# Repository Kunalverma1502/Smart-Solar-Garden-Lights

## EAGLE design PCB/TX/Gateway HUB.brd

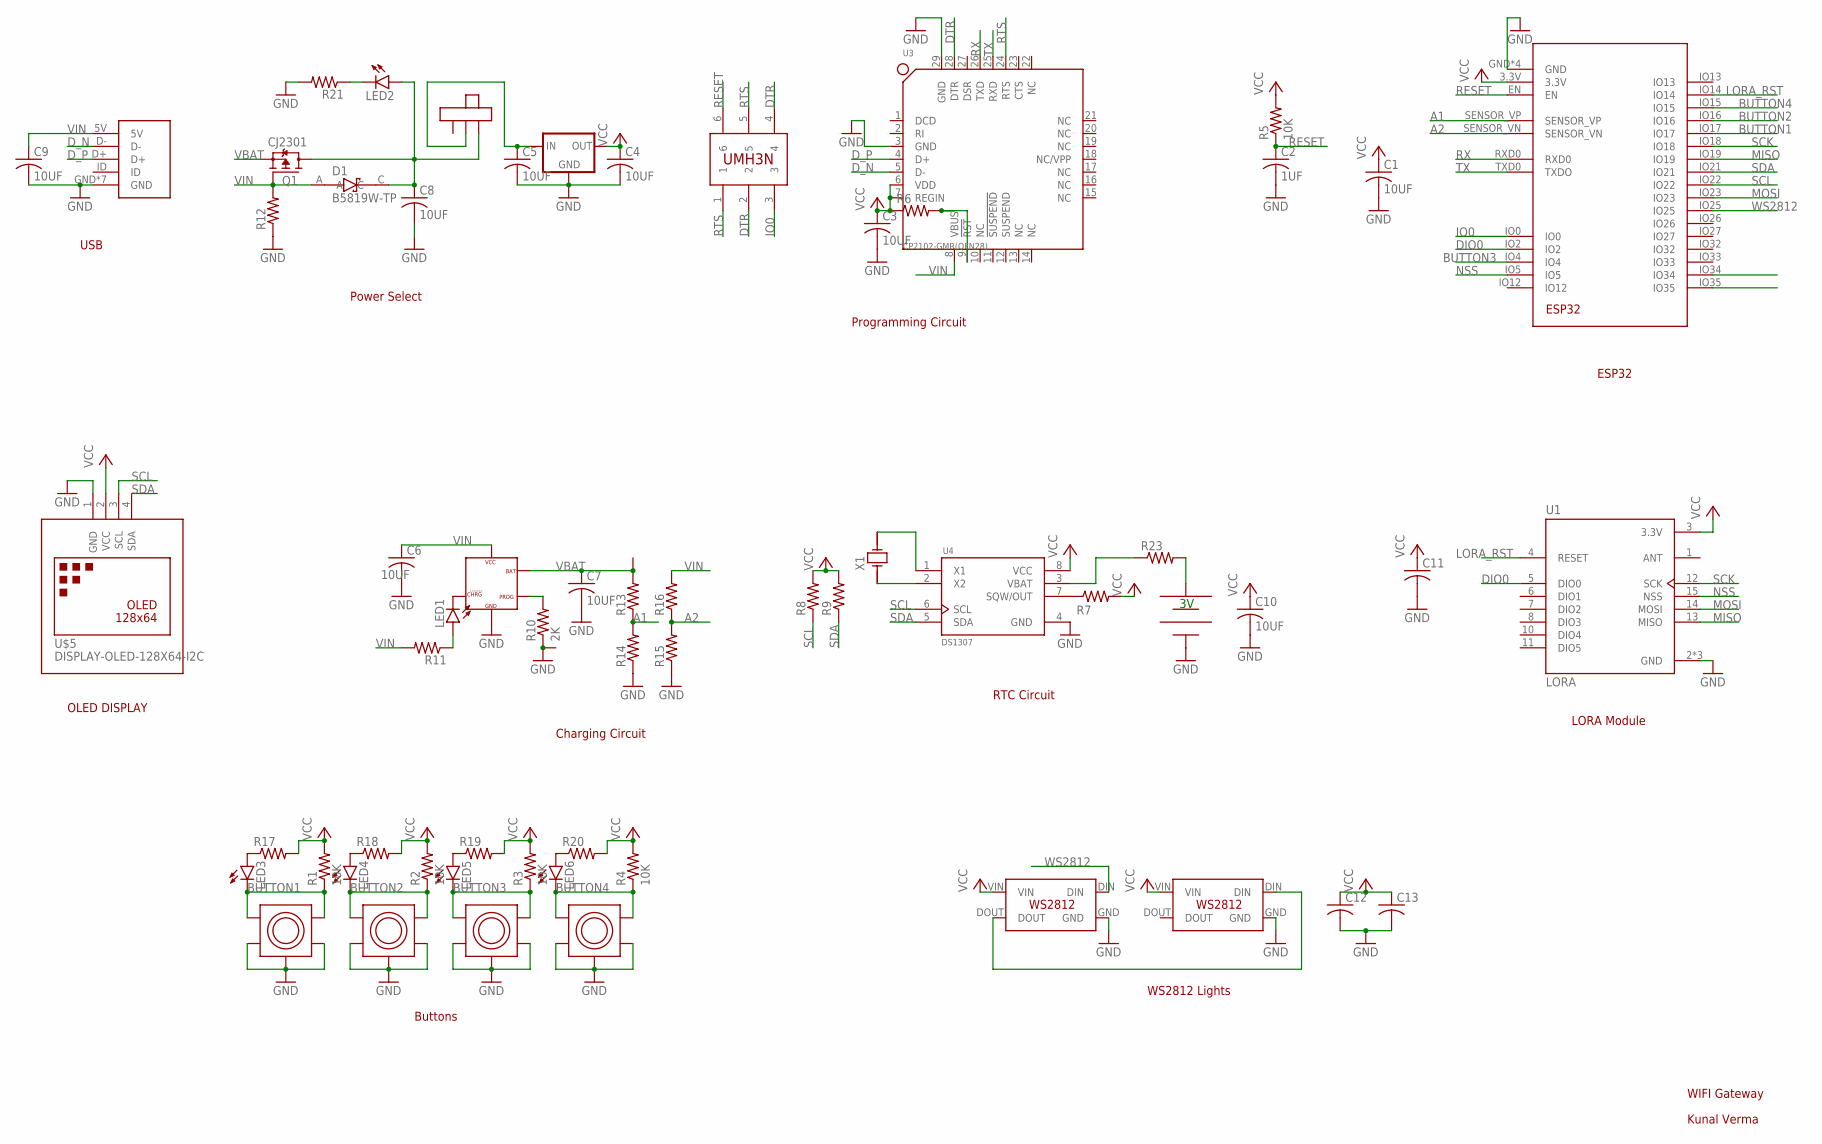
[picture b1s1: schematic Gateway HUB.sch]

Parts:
C1, C3, C4, C5, C6, C7, C8, C9, C10: 10UF; C0603
C2: 1UF; C0603
C11, C12, C13: C-USC0603; C0603
D1: B5819W-TP; SOD3716X135N
IC1: V_REG3.3MP; SOT223
LED1, LED2, LED3, LED4, LED5, LED6: LEDSML0603; SML0603
Q1: CJ2301; SOT95P230X110-3N
R1, R2, R3, R4, R5: 10K; R0603
R6, R7, R8, R9, R11, R12, R13, R14, R15, R16, R17, R18, R19, R20, R21, R23: R-US_R0603; R0603
R10: 2K; R0603
U1: LORA; XCVR_RA-01H
U2: ESP32; MODULE_ESP-WROOM-32
U3: CP2102-GMR(QFN28); QFN28G_0.5-5X5MM
U4: DS1307; SOIC127P600X175-8N
U5: TP4054; SOT23-3
U$1, U$2, U$3, U$4: PUSHBUTTON; B3W-4105
U$5: DISPLAY-OLED-128X64-I2C
U$6: COIN_CELL_HOLDER; CR2032-BS-6-1
U$7: UMH3N
U$8: MICROUSB; USB
U$9: SELF-TOOGLE-SWITCH
U$10, U$11: PAD; PADS
U$12, U$13: WS2812SMD-2020; SMD-2020
X1: CRYSTAL_38T-32.768KHZ; XTAL_AB38T-32.768KHZ

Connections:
A1: R13.1, R14.2, U2.SENSOR_VP
A2: R15.2, R16.1, U2.SENSOR_VN
BUTTON1: LED3.C, R1.1, U2.IO17, U$1.P$1, U$1.P$4
BUTTON2: LED4.C, R2.1, U2.IO16, U$2.P$1, U$2.P$4
BUTTON3: LED5.C, R3.1, U2.IO4, U$3.P$1, U$3.P$4
BUTTON4: LED6.C, R4.1, U2.IO15, U$4.P$1, U$4.P$4
DIO0: U1.5 (DIO0), U2.IO2
DTR: U3.28 (DTR), U$7.2, U$7.4
D_N: U3.5 (D-), U$8.D-
D_P: U3.4 (D+), U$8.D+
GND: C1.2, C2.2, C3.2, C4.2, C5.2, C6.2, C7.2, C8.2, C9.2, C10.2, C11.2, C12.2, C13.2, IC1.GND, R10.1, R12.1, R14.1, R15.1, R21.2, U1.2 (GND), U1.9 (GND), U1.16 (GND), U2.GND, U2.GND1 (GND), U2.GND2 (GND), U2.GND3 (GND), U3.3 (GND), U3.29 (GND), U4.4 (GND), U5.2, U$1.P$2, U$1.P$3, U$1.P$5, U$2.P$2, U$2.P$3, U$2.P$5, U$3.P$2, U$3.P$3, U$3.P$5, U$4.P$2, U$4.P$3, U$4.P$5, U$5.1 (GND), U$6.-, U$8.GND, U$8.GND1 (GND), U$8.GND2 (GND), U$8.GND3 (GND), U$8.GND4 (GND), U$8.GND5 (GND), U$8.GND6 (GND), U$11.P$1, U$12.GND, U$13.GND
IO0: U2.IO0, U$7.3
LORA_RST: U1.4 (RESET), U2.IO14
MISO: U1.13 (MISO), U2.IO19
MOSI: U1.14 (MOSI), U2.IO23
unnamed: R23.1, U4.3 (VBAT)
unnamed: R6.2, U3.9 (!RST)
unnamed: R7.1, U4.7 (SQW/OUT)
unnamed: C5.1, IC1.VIN (IN), U$9.2
unnamed: U4.2 (X2), X1.1
unnamed: U4.1 (X1), X1.2
unnamed: R10.2, U5.5
unnamed: LED1.C, U5.1
unnamed: C8.1, D1.C, LED2.A, Q1.3 (D), U$9.3
unnamed: LED1.A, R11.1
unnamed: LED3.A, R17.1
unnamed: LED4.A, R18.1
unnamed: LED5.A, R19.1
unnamed: LED6.A, R20.1
unnamed: LED2.C, R21.1
unnamed: U$12.DOUT, U$13.DIN
unnamed: R23.2, U$6.+
NSS: U1.15 (NSS), U2.IO5
RESET: C2.1, R5.1, U2.EN, U$7.6
RTS: U3.24 (RTS), U$7.1, U$7.5
RX: U2.RXD0, U3.26 (TXD)
SCK: U1.12 (SCK), U2.IO18
SCL: R8.1, U2.IO22, U4.6 (SCL), U$5.3 (SCL)
SDA: R9.1, U2.IO21, U4.5 (SDA), U$5.4 (SDA)
TX: U2.TXD0 (TXDO), U3.25 (RXD)
VBAT: C7.1, Q1.2 (S), R13.2, U5.3, U$10.P$1
VCC: C1.1, C3.1, C4.1, C10.1, C11.1, C12.1, C13.1, IC1.VOUT (OUT), IC1.VOUT1 (OUT), R1.2, R2.2, R3.2, R4.2, R5.2, R6.1, R7.2, R8.2, R9.2, R17.2, R18.2, R19.2, R20.2, U1.3 (3.3V), U2.3.3V, U3.6 (VDD), U3.7 (REGIN), U4.8 (VCC), U$5.2 (VCC), U$12.VIN, U$13.VIN
VIN: C6.1, C9.1, D1.A, Q1.1 (G), R11.2, R12.2, R16.2, U3.8 (VBUS), U5.4, U$8.5V
WS2812: U2.IO25, U$12.DIN

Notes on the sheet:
WIFI Gateway
Kunal Verma
Buttons
WS2812 Lights
OLED DISPLAY
Charging Circuit
RTC Circuit
LORA Module
ESP32
Programming Circuit
Power Select
USB

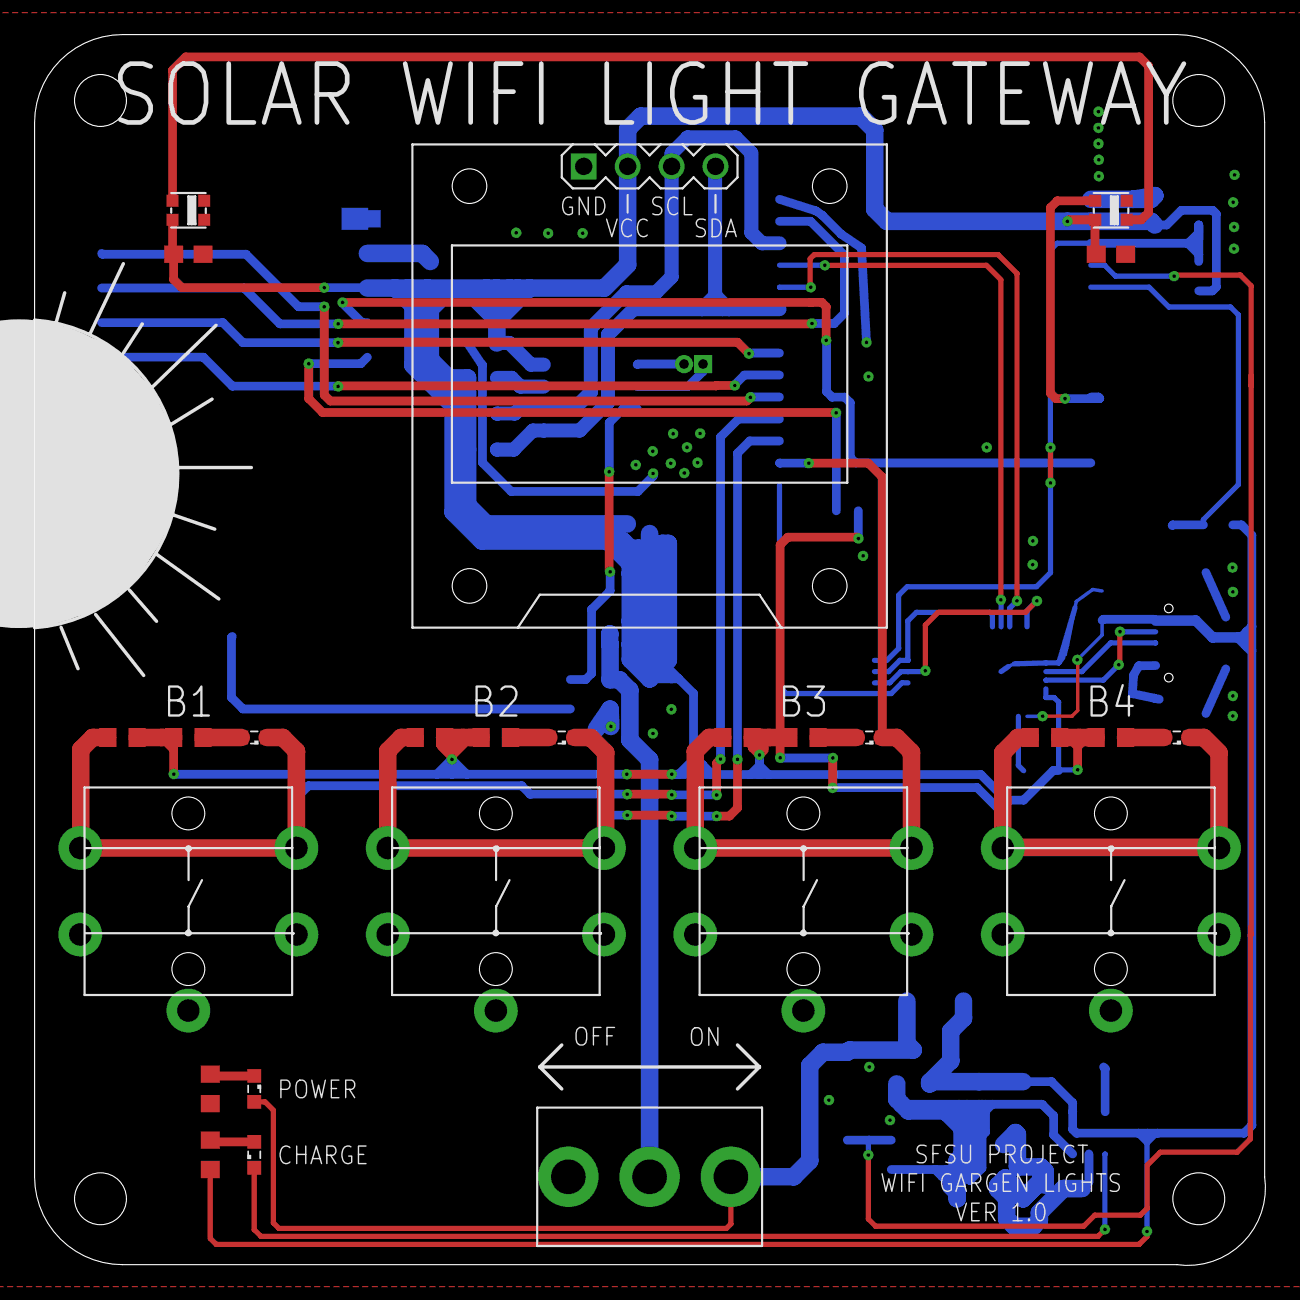
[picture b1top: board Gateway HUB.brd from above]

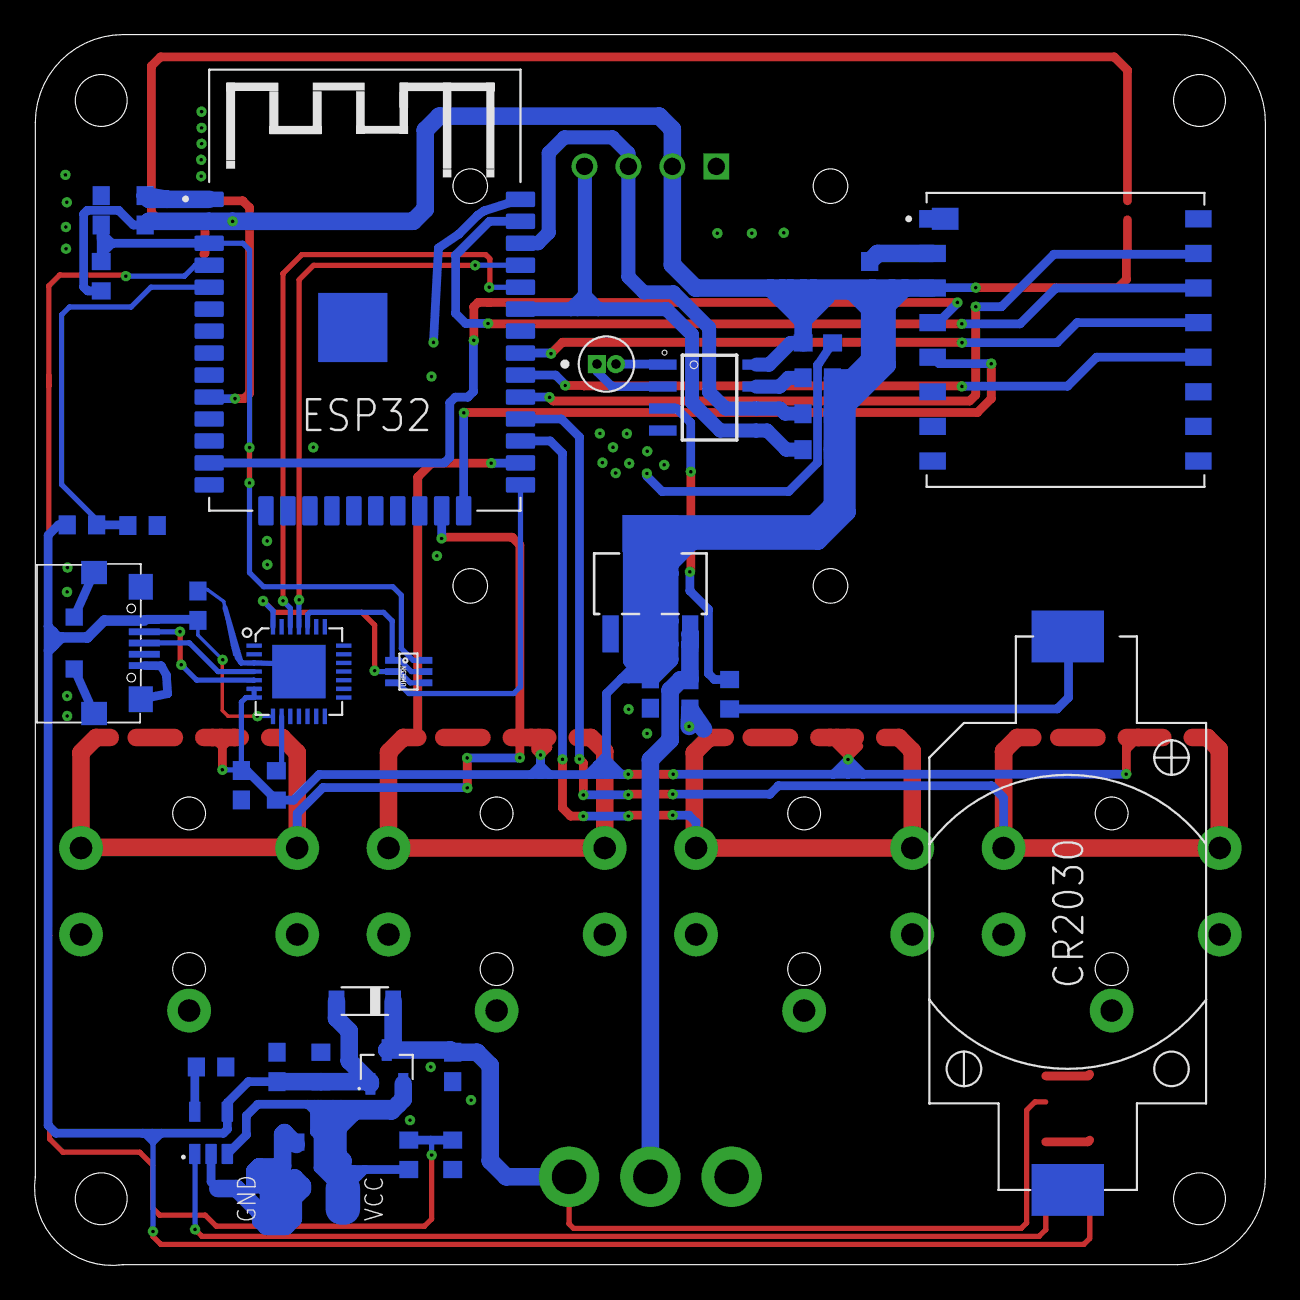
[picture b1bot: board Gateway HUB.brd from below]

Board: 2 copper layers, 71.2 x 71.2 mm, 63 parts (37 on the bottom side), 44 nets.

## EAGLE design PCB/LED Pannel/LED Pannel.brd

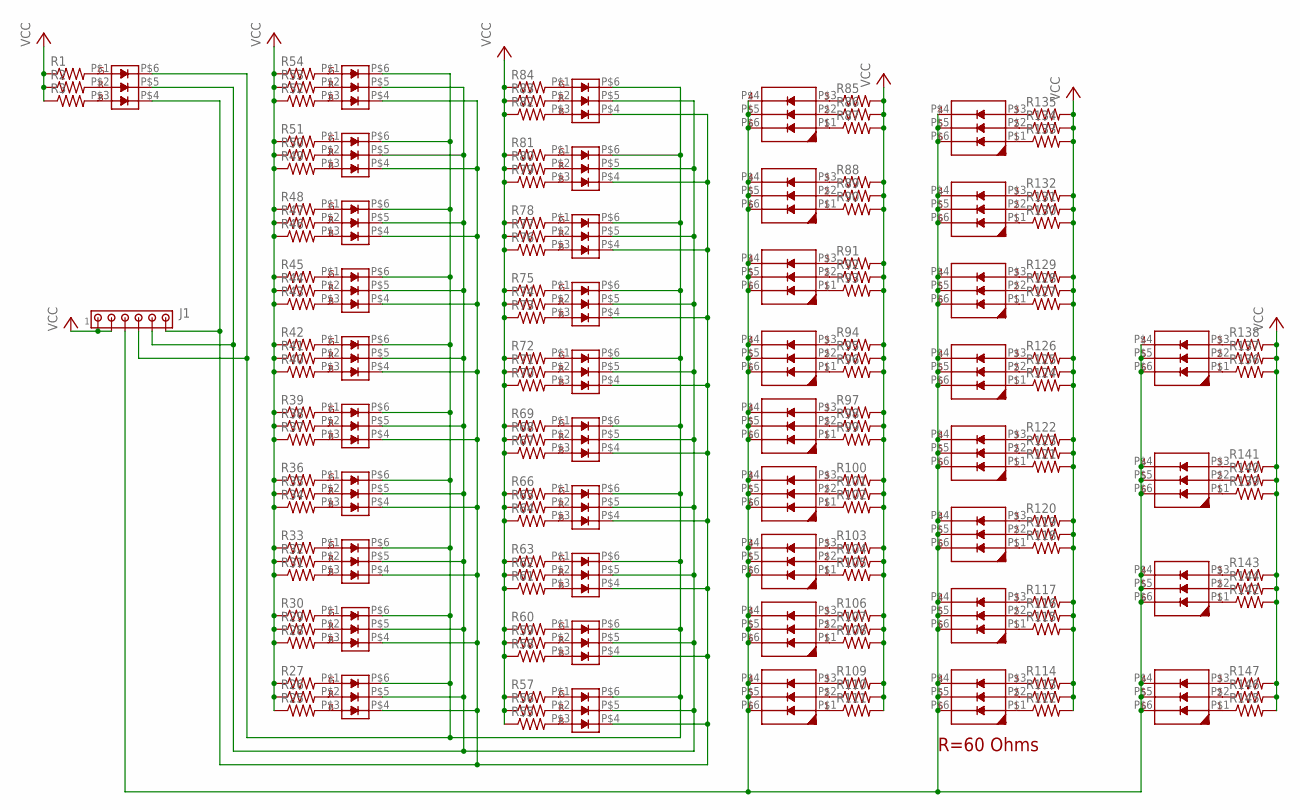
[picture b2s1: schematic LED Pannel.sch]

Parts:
J1: MTA06-156; 1X6MTA
R1, R2, R3, R25, R26, R27, R28, R29, R30, R31, R32, R33, R34, R35, R36, R37, R38, R39, R40, R41, R42, R43, R44, R45, R46, R47, R48, R49, R50, R51, R52, R53, R54, R55, R56, R57, R58, R59, R60, R61, R62, R63, R64, R65, R66, R67, R68, R69, R70, R71, R72, R73, R74, R75, R76, R77, R78, R79, R80, R81, R82, R83, R84, R85, R86, R87, R88, R89, R90, R91, R92, R93, R94, R95, R96, R97, R98, R99, R100, R101, R102, R103, R104, R105, R106, R107, R108, R109, R110, R111, R112, R113, R114, R115, R116, R117, R118, R119, R120, R121, R122, R123, R124, R125, R126, R127, R128, R129, R130, R131, R132, R133, R134, R135, R136, R137, R138, R139, R140, R141, R142, R143, R144, R145, R146, R147: R-US_R0603; R0603
U$1, U$2, U$3, U$4, U$5, U$6, U$7, U$8, U$9, U$10, U$17, U$18, U$19, U$20, U$21, U$22, U$23, U$24, U$25, U$26, U$27: RGB_LED; 5050
U$11, U$12, U$13, U$14, U$15, U$16, U$35, U$36, U$37, U$38, U$47, U$48, U$49, U$50, U$51, U$52, U$53, U$54, U$55, U$56, U$57: WHITE_LED; 5050

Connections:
unnamed: R1.2, U$27.P$1
unnamed: R2.2, U$27.P$2
unnamed: R3.2, U$27.P$3
unnamed: J1.4, U$1.P$6, U$2.P$6, U$3.P$6, U$4.P$6, U$5.P$6, U$6.P$6, U$7.P$6, U$8.P$6, U$9.P$6, U$10.P$6, U$17.P$6, U$18.P$6, U$19.P$6, U$20.P$6, U$21.P$6, U$22.P$6, U$23.P$6, U$24.P$6, U$25.P$6, U$26.P$6, U$27.P$6
unnamed: J1.5, U$1.P$5, U$2.P$5, U$3.P$5, U$4.P$5, U$5.P$5, U$6.P$5, U$7.P$5, U$8.P$5, U$9.P$5, U$10.P$5, U$17.P$5, U$18.P$5, U$19.P$5, U$20.P$5, U$21.P$5, U$22.P$5, U$23.P$5, U$24.P$5, U$25.P$5, U$26.P$5, U$27.P$5
unnamed: J1.6, U$1.P$4, U$2.P$4, U$3.P$4, U$4.P$4, U$5.P$4, U$6.P$4, U$7.P$4, U$8.P$4, U$9.P$4, U$10.P$4, U$17.P$4, U$18.P$4, U$19.P$4, U$20.P$4, U$21.P$4, U$22.P$4, U$23.P$4, U$24.P$4, U$25.P$4, U$26.P$4, U$27.P$4
unnamed: J1.3, U$11.P$4, U$11.P$5, U$11.P$6, U$12.P$4, U$12.P$5, U$12.P$6, U$13.P$4, U$13.P$5, U$13.P$6, U$14.P$4, U$14.P$5, U$14.P$6, U$15.P$4, U$15.P$5, U$15.P$6, U$16.P$4, U$16.P$5, U$16.P$6, U$35.P$4, U$35.P$5, U$35.P$6, U$36.P$4, U$36.P$5, U$36.P$6, U$37.P$4, U$37.P$5, U$37.P$6, U$38.P$4, U$38.P$5, U$38.P$6, U$47.P$4, U$47.P$5, U$47.P$6, U$48.P$4, U$48.P$5, U$48.P$6, U$49.P$4, U$49.P$5, U$49.P$6, U$50.P$4, U$50.P$5, U$50.P$6, U$51.P$4, U$51.P$5, U$51.P$6, U$52.P$4, U$52.P$5, U$52.P$6, U$53.P$4, U$53.P$5, U$53.P$6, U$54.P$4, U$54.P$5, U$54.P$6, U$55.P$4, U$55.P$5, U$55.P$6, U$56.P$4, U$56.P$5, U$56.P$6, U$57.P$4, U$57.P$5, U$57.P$6
unnamed: R25.2, U$26.P$3
unnamed: R26.2, U$26.P$2
unnamed: R28.2, U$25.P$3
unnamed: R29.2, U$25.P$2
unnamed: R30.2, U$25.P$1
unnamed: R27.2, U$26.P$1
unnamed: R31.2, U$24.P$3
unnamed: R32.2, U$24.P$2
unnamed: R33.2, U$24.P$1
unnamed: R34.2, U$23.P$3
unnamed: R35.2, U$23.P$2
unnamed: R36.2, U$23.P$1
unnamed: R37.2, U$22.P$3
unnamed: R38.2, U$22.P$2
unnamed: R39.2, U$22.P$1
unnamed: R40.2, U$21.P$3
unnamed: R41.2, U$21.P$2
unnamed: R42.2, U$21.P$1
unnamed: R43.2, U$20.P$3
unnamed: R44.2, U$20.P$2
unnamed: R45.2, U$20.P$1
unnamed: R46.2, U$19.P$3
unnamed: R47.2, U$19.P$2
unnamed: R48.2, U$19.P$1
unnamed: R49.2, U$18.P$3
unnamed: R50.2, U$18.P$2
unnamed: R51.2, U$18.P$1
unnamed: R52.2, U$17.P$3
unnamed: R53.2, U$17.P$2
unnamed: R54.2, U$17.P$1
unnamed: R56.2, U$1.P$2
unnamed: R57.2, U$1.P$1
unnamed: R55.2, U$1.P$3
unnamed: R58.2, U$2.P$3
unnamed: R59.2, U$2.P$2
unnamed: R60.2, U$2.P$1
unnamed: R61.2, U$3.P$3
unnamed: R62.2, U$3.P$2
unnamed: R63.2, U$3.P$1
unnamed: R64.2, U$4.P$3
unnamed: R65.2, U$4.P$2
unnamed: R66.2, U$4.P$1
unnamed: R68.2, U$5.P$2
unnamed: R69.2, U$5.P$1
unnamed: R67.2, U$5.P$3
unnamed: R70.2, U$6.P$3
unnamed: R71.2, U$6.P$2
unnamed: R72.2, U$6.P$1
unnamed: R73.2, U$7.P$3
unnamed: R74.2, U$7.P$2
unnamed: R75.2, U$7.P$1
unnamed: R76.2, U$8.P$3
unnamed: R77.2, U$8.P$2
unnamed: R78.2, U$8.P$1
unnamed: R79.2, U$9.P$3
unnamed: R80.2, U$9.P$2
unnamed: R81.2, U$9.P$1
unnamed: R82.2, U$10.P$3
unnamed: R83.2, U$10.P$2
unnamed: R84.2, U$10.P$1
unnamed: R85.1, U$49.P$3
unnamed: R86.1, U$49.P$2
unnamed: R87.1, U$49.P$1
unnamed: R88.1, U$48.P$3
unnamed: R89.1, U$48.P$2
unnamed: R90.1, U$48.P$1
unnamed: R91.1, U$47.P$3
unnamed: R92.1, U$47.P$2
unnamed: R93.1, U$47.P$1
unnamed: R95.1, U$16.P$2
unnamed: R96.1, U$16.P$1
unnamed: R94.1, U$16.P$3
unnamed: R97.1, U$15.P$3
unnamed: R98.1, U$15.P$2
unnamed: R99.1, U$15.P$1
unnamed: R100.1, U$14.P$3
unnamed: R101.1, U$14.P$2
unnamed: R102.1, U$14.P$1
unnamed: R103.1, U$13.P$3
unnamed: R104.1, U$13.P$2
unnamed: R105.1, U$13.P$1
unnamed: R106.1, U$12.P$3
unnamed: R107.1, U$12.P$2
unnamed: R108.1, U$12.P$1
unnamed: R109.1, U$11.P$3
unnamed: R110.1, U$11.P$2
unnamed: R111.1, U$11.P$1
unnamed: R112.1, U$57.P$1
unnamed: R113.1, U$57.P$2
unnamed: R114.1, U$57.P$3
unnamed: R115.1, U$56.P$1
unnamed: R116.1, U$56.P$2
unnamed: R117.1, U$56.P$3
unnamed: R118.1, U$55.P$1
unnamed: R119.1, U$55.P$2
unnamed: R120.1, U$55.P$3
unnamed: R121.1, U$54.P$1
unnamed: R122.1, U$54.P$3
unnamed: R123.1, U$54.P$2
unnamed: R124.1, U$53.P$1
unnamed: R125.1, U$53.P$2
unnamed: R126.1, U$53.P$3
unnamed: R127.1, U$52.P$1
unnamed: R128.1, U$52.P$2
unnamed: R129.1, U$52.P$3
unnamed: R130.1, U$51.P$1
unnamed: R131.1, U$51.P$2
unnamed: R132.1, U$51.P$3
unnamed: R133.1, U$50.P$1
unnamed: R134.1, U$50.P$2
unnamed: R135.1, U$50.P$3
unnamed: R136.1, U$38.P$1
unnamed: R137.1, U$38.P$2
unnamed: R138.1, U$38.P$3
unnamed: R139.1, U$37.P$1
unnamed: R140.1, U$37.P$2
unnamed: R141.1, U$37.P$3
unnamed: R142.1, U$36.P$1
unnamed: R143.1, U$36.P$3
unnamed: R144.1, U$36.P$2
unnamed: R145.1, U$35.P$1
unnamed: R146.1, U$35.P$2
unnamed: R147.1, U$35.P$3
VCC: J1.1, J1.2, R1.1, R2.1, R3.1, R25.1, R26.1, R27.1, R28.1, R29.1, R30.1, R31.1, R32.1, R33.1, R34.1, R35.1, R36.1, R37.1, R38.1, R39.1, R40.1, R41.1, R42.1, R43.1, R44.1, R45.1, R46.1, R47.1, R48.1, R49.1, R50.1, R51.1, R52.1, R53.1, R54.1, R55.1, R56.1, R57.1, R58.1, R59.1, R60.1, R61.1, R62.1, R63.1, R64.1, R65.1, R66.1, R67.1, R68.1, R69.1, R70.1, R71.1, R72.1, R73.1, R74.1, R75.1, R76.1, R77.1, R78.1, R79.1, R80.1, R81.1, R82.1, R83.1, R84.1, R85.2, R86.2, R87.2, R88.2, R89.2, R90.2, R91.2, R92.2, R93.2, R94.2, R95.2, R96.2, R97.2, R98.2, R99.2, R100.2, R101.2, R102.2, R103.2, R104.2, R105.2, R106.2, R107.2, R108.2, R109.2, R110.2, R111.2, R112.2, R113.2, R114.2, R115.2, R116.2, R117.2, R118.2, R119.2, R120.2, R121.2, R122.2, R123.2, R124.2, R125.2, R126.2, R127.2, R128.2, R129.2, R130.2, R131.2, R132.2, R133.2, R134.2, R135.2, R136.2, R137.2, R138.2, R139.2, R140.2, R141.2, R142.2, R143.2, R144.2, R145.2, R146.2, R147.2

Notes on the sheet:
R=60 Ohms

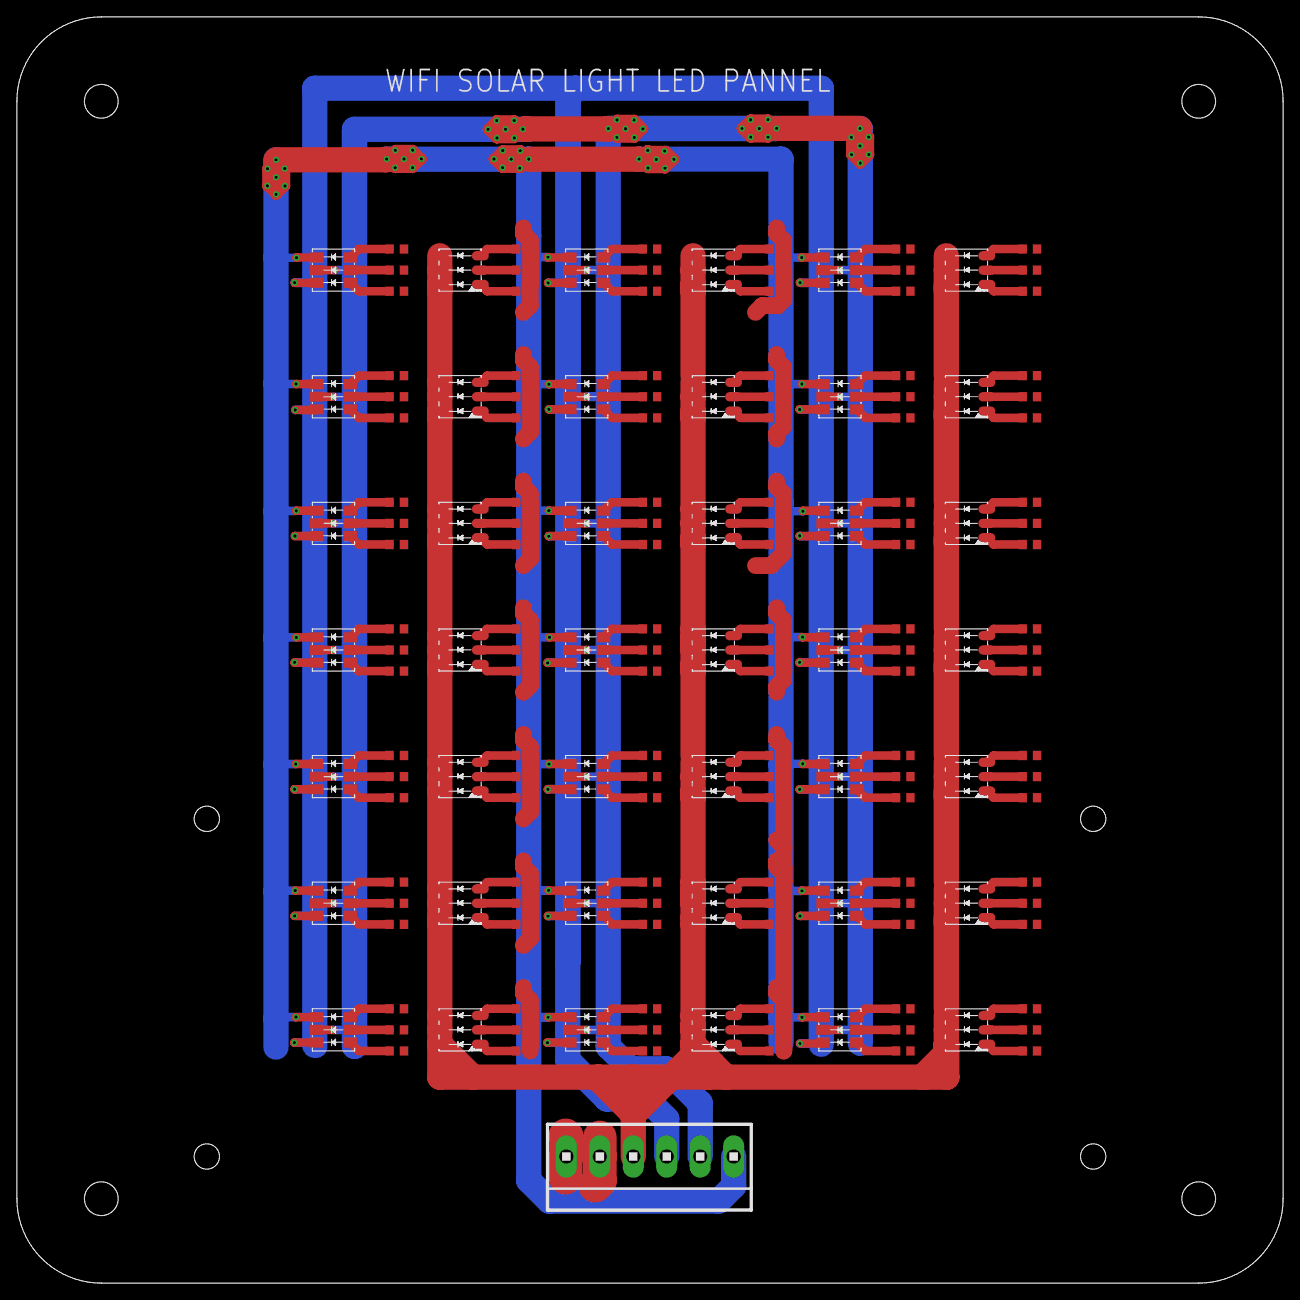
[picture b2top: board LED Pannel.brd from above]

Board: 2 copper layers, 150.0 x 150.0 mm, 169 parts (0 on the bottom side), 131 nets.

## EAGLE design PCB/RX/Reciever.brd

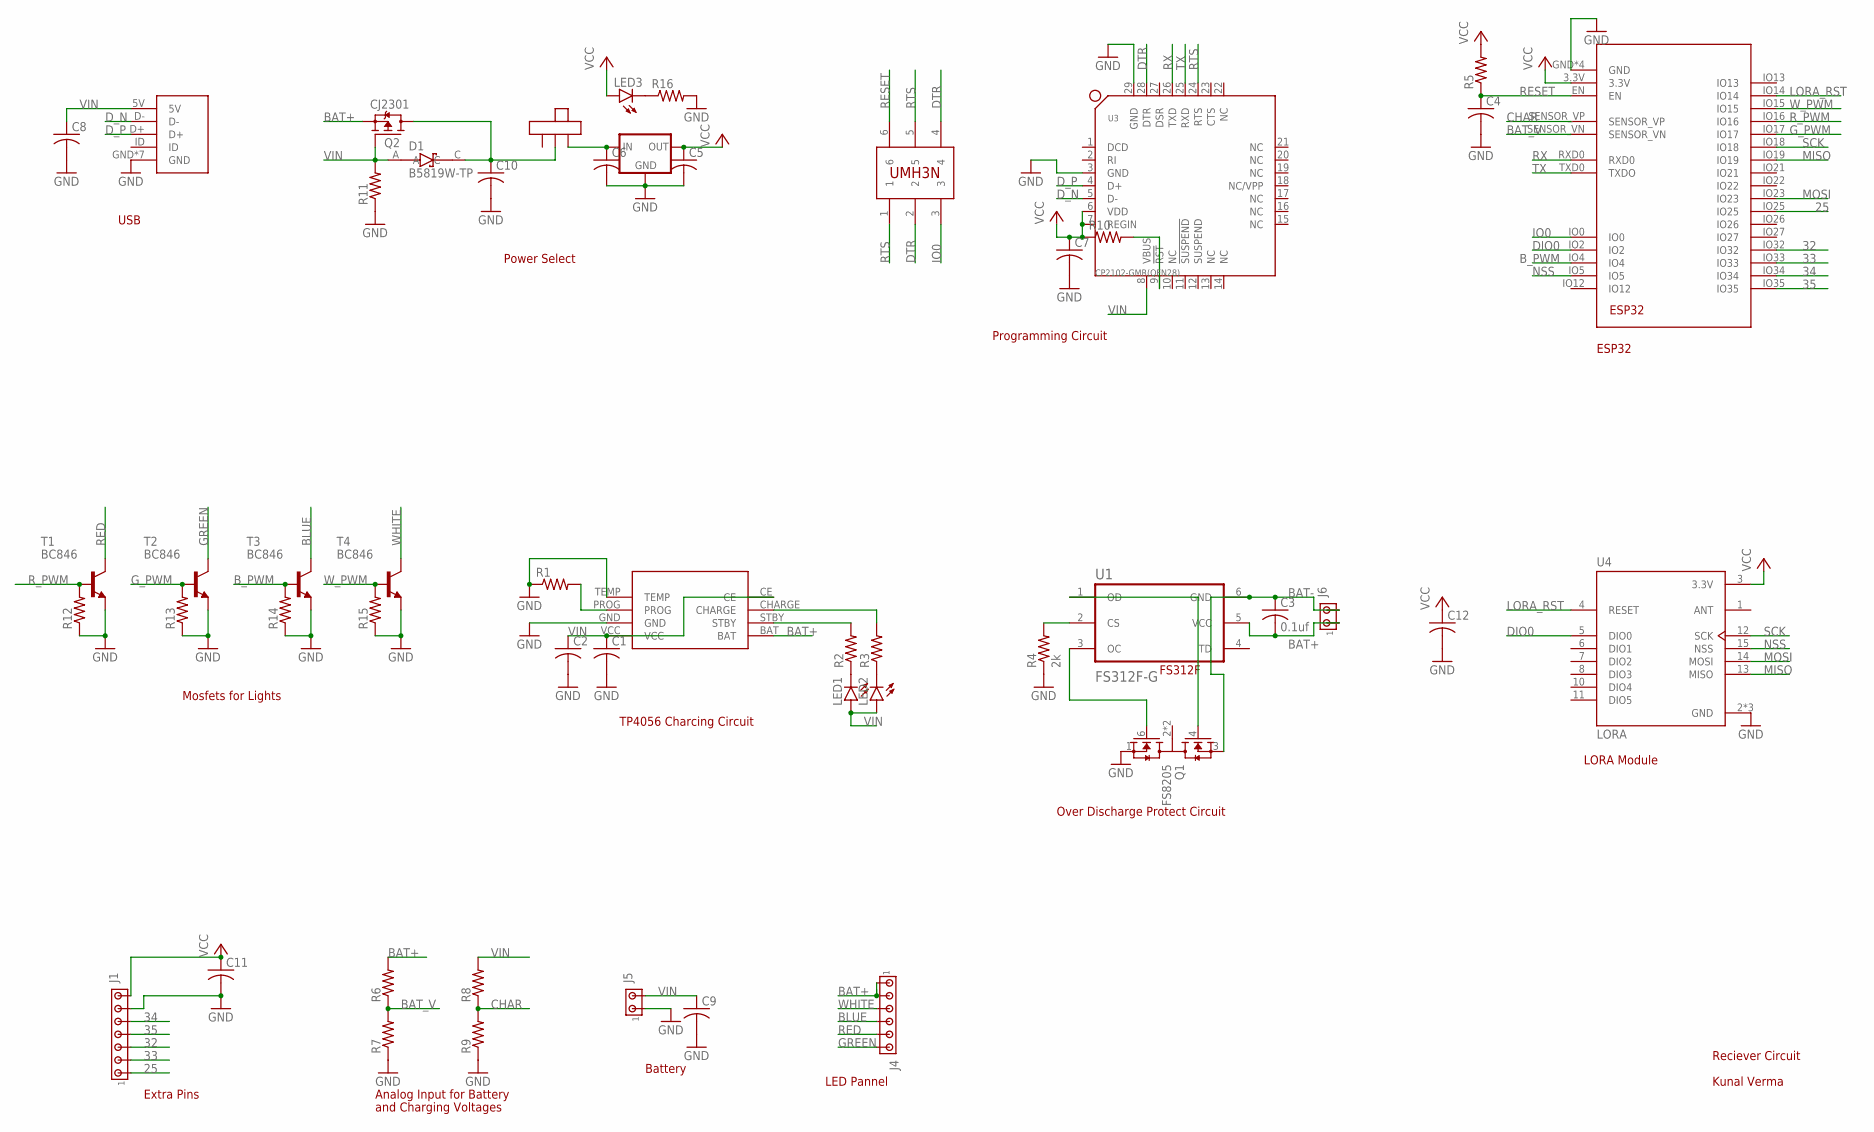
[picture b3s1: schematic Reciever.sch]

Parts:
C1, C2, C4, C5, C6, C7, C8, C9, C10, C11, C12: C-USC0603; C0603
C3: 0.1uf; C0603
D1: B5819W-TP; SOD3716X135N
IC1: V_REG3.3MP; SOT223
J1: MTA07-100; 10X07MTA
J4: MTA06-156; 1X6MTA
J5, J6: MTA02-156; 1X2MTA
LED1, LED2: LEDCHIPLED_0603; CHIPLED_0603
LED3: LEDCHIP-LED0603; CHIP-LED0603
Q1: FS8205; SOT95P280X145-6N
Q2: CJ2301; SOT95P230X110-3N
R1, R2, R3, R5, R6, R7, R8, R9, R10, R11, R12, R13, R14, R15, R16: R-US_R0603; R0603
R4: 2k; R0603
T1, T2, T3, T4: BC846; SOT23
U1: FS312F-G; SOT223-6
U2: ESP32; MODULE_ESP-WROOM-32
U3: CP2102-GMR(QFN28); QFN28G_0.5-5X5MM
U4: LORA; XCVR_RA-01H
U$1: TP4056
U$2: SELF-TOOGLE-SWITCH
U$3: MICROUSB; USB
U$4: UMH3N

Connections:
25: J1.1, U2.IO25
32: J1.3, U2.IO32
33: J1.2, U2.IO33
34: J1.5, U2.IO34
35: J1.4, U2.IO35
BAT+: C3.2, J4.1, J4.2, J6.1, Q2.2 (S), R6.2, U1.5 (VCC), U$1.BAT
BAT-: C3.1, J6.2, Q1.3 (S2), U1.6 (GND)
BAT_V: R6.1, R7.2, U2.SENSOR_VN
BLUE: J4.4, T3.3 (C)
B_PWM: R14.2, T3.1 (B), U2.IO4
CHAR: R8.1, R9.2, U2.SENSOR_VP
DIO0: U2.IO2, U4.5 (DIO0)
DTR: U3.28 (DTR), U$4.2, U$4.4
D_N: U3.5 (D-), U$3.D-
D_P: U3.4 (D+), U$3.D+
GND: C1.2, C2.2, C4.2, C5.2, C6.2, C7.2, C8.2, C9.2, C10.2, C11.2, C12.2, IC1.GND, J1.6, J5.1, Q1.1 (S1), R1.1, R4.1, R7.1, R9.1, R11.1, R12.1, R13.1, R14.1, R15.1, R16.2, T1.2 (E), T2.2 (E), T3.2 (E), T4.2 (E), U2.GND, U2.GND1 (GND), U2.GND2 (GND), U2.GND3 (GND), U3.3 (GND), U3.29 (GND), U4.2 (GND), U4.9 (GND), U4.16 (GND), U$1.GND, U$1.TEMP, U$3.GND, U$3.GND1 (GND), U$3.GND2 (GND), U$3.GND3 (GND), U$3.GND4 (GND), U$3.GND5 (GND), U$3.GND6 (GND)
GREEN: J4.6, T2.3 (C)
G_PWM: R13.2, T2.1 (B), U2.IO17
IO0: U2.IO0, U$4.3
LORA_RST: U2.IO14, U4.4 (RESET)
MISO: U2.IO19, U4.13 (MISO)
MOSI: U2.IO23, U4.14 (MOSI)
unnamed: R1.2, U$1.PROG
unnamed: LED1.C, R2.1
unnamed: R4.2, U1.2 (CS)
unnamed: LED2.C, R3.1
unnamed: Q1.4 (G2), U1.1 (OD)
unnamed: R2.2, U$1.STBY
unnamed: R3.2, U$1.CHARGE
unnamed: Q1.6 (G1), U1.3 (OC)
unnamed: C10.1, D1.C, Q2.3 (D), U$2.2
unnamed: R10.2, U3.9 (!RST)
unnamed: LED3.C, R16.1
unnamed: C6.1, IC1.VIN (IN), U$2.3
NSS: U2.IO5, U4.15 (NSS)
RED: J4.5, T1.3 (C)
RESET: C4.1, R5.1, U2.EN, U$4.6
RTS: U3.24 (RTS), U$4.1, U$4.5
RX: U2.RXD0, U3.26 (TXD)
R_PWM: R12.2, T1.1 (B), U2.IO16
SCK: U2.IO18, U4.12 (SCK)
TX: U2.TXD0 (TXDO), U3.25 (RXD)
VCC: C5.1, C7.1, C11.1, C12.1, IC1.VOUT (OUT), IC1.VOUT1 (OUT), J1.7, LED3.A, R5.2, R10.1, U2.3.3V, U3.6 (VDD), U3.7 (REGIN), U4.3 (3.3V)
VIN: C1.1, C2.1, C8.1, C9.1, D1.A, J5.2, LED1.A, LED2.A, Q2.1 (G), R8.2, R11.2, U3.8 (VBUS), U$1.CE, U$1.VCC, U$3.5V
WHITE: J4.3, T4.3 (C)
W_PWM: R15.2, T4.1 (B), U2.IO15

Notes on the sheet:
USB
Power Select
Programming Circuit
ESP32
Mosfets for Lights
TP4056 Charcing Circuit
Over Discharge Protect Circuit
LORA Module
Extra Pins
Analog Input for Battery
and Charging Voltages
Battery
LED Pannel
Reciever Circuit
Kunal Verma

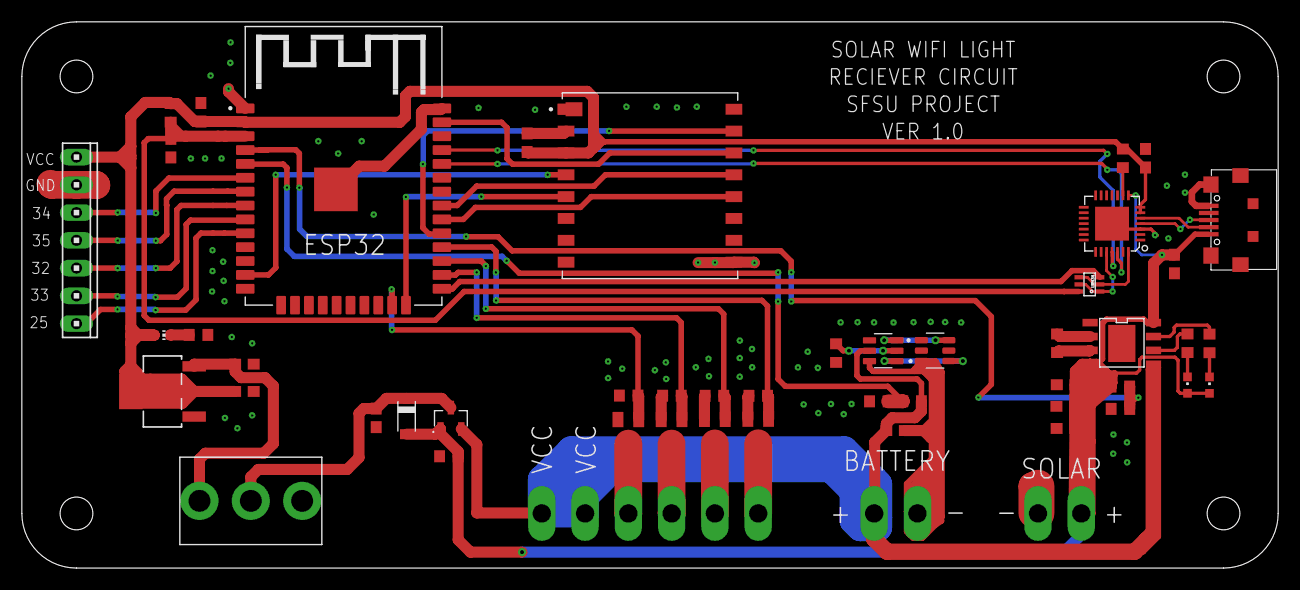
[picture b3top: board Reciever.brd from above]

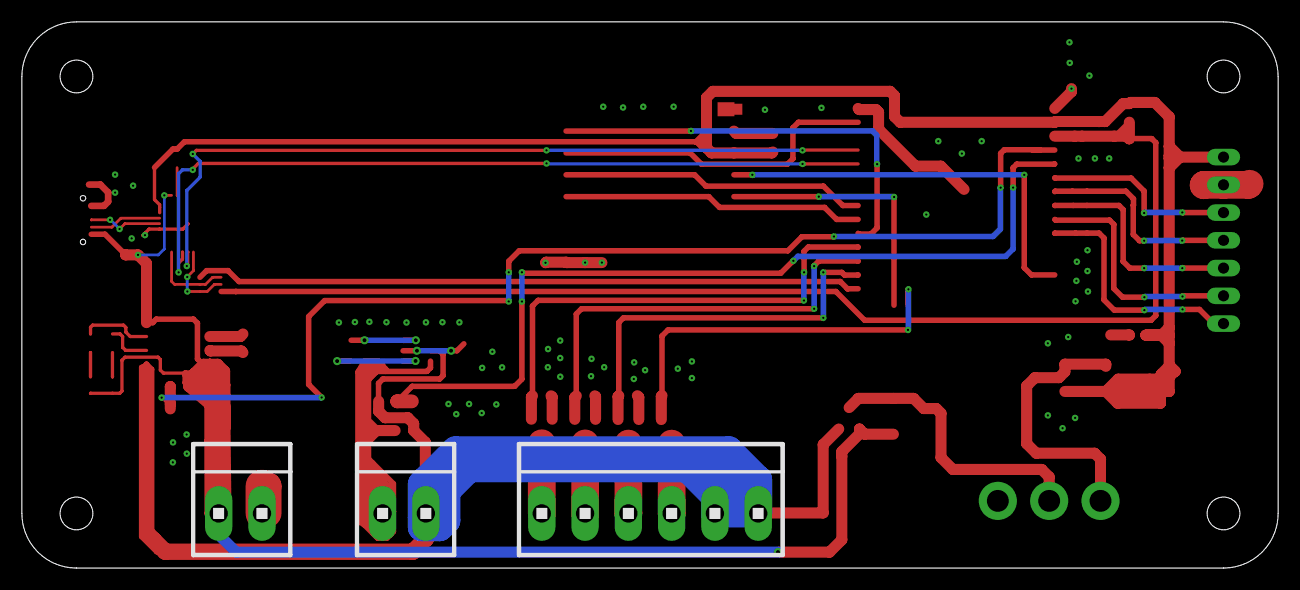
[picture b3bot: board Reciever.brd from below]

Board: 2 copper layers, 115.0 x 50.0 mm, 51 parts (3 on the bottom side), 46 nets.

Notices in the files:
parts and their libraries:
diy-modules: Released under the Creative Commons Attribution 4.0 International License: http://creativecommons.org/licenses/by/4.0
